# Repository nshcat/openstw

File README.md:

# openstw

A project aiming to design a physical replica of a German Sp Dr S60 relais signal box panel (_Stelltisch_) with a software simulation of local railway traffic behind it, in order to offer a compelling simulation of the day-to-day work of a signal box operator (_Fahrdienstleiter_).

## Project goals
- **A depiction of a Sp Dr S60 Stelltisch that is as realistic as possible** - This is pretty much the main goal for me. Unlike many other projects on the internet that already saw the light of day, I am not planning on making any compromises when it comes to the visual and functional design of the Stelltisch and its tiles. Even though that is likely never going to happen, I'd want it to be useable as a training aid for train routing controllers, even if only in theory.

- **Easy extensibility when adapting to new Betriebsstellen** - The system should be very modular and easy to configure, such that building replicas of any of the real German Betriebsstellen that employ a Sp Dr S60 signal box is as easy and frictionless as possible. Of course, local oddities will almost always require some degree of customization, such as custom tiles that feature specific colours and signal placements, but my goal is to reduce this work as much as possible, and make it as easy as possible.

- **As little expensive tools needed as possible** - I want the whole project to be buildable with nothing more than a run-of-the-mill 3D printer, access to a PCB manufacturing and assembly service and a set of screwdrivers. This includes not having to pay tons of money for software licenses!

- And of course, **Be completely Open-Source!** - To me, this also implies that all the tools used to make this project a reality should be open-source as well.

## Non-goals
- **Interfacing with model train setups** - I personally am neither interested in nor experienced with model train setups, and thus this project will not be designed or implemented with that in mind. Although the already existing software and hardware architecture design does leave the possibility open, if anyone else dares to try :)

- **Have everything be hand-solderable** - I have decided against this right from the start. The small size of the Stelltisch tiles make it almost a neccasity to use very small SMT components, and since access to PCB assembly is easy and comparatively cheap nowadays, I felt that it would be silly to restrict my design to being hand solderable and risk compromising my goal of realism. And one can still use a stencil, solder paste and a cheap mini hot plate to assemble the boards, if so desired.

## Repository structure

Each sub folder contains its own README file with more detailed information about that specific component of the project. Right now, the project consists of the following components:

 - `hardware`: Contains design files for the various PCBs and 3d-printed components used in the project that make up the physical Stelltisch, and act as the simulator frontend.
 - `software`: The software that simulates the signal box, including simulated time tables and train traffic. This acts as the simulator backend.
 - `firmware`: Firmware for all PCBs that contain a programmable microcontroller. The firmware handles communication with the simulator backend via CAN bus, and controlling and supervising the LEDs and input elements of each Stelltisch tile.

## Glossary
- **Stellwerk** - German term for a signalling box.
- **Fahrdienstleiter** - German term for a signal box operator.
- **Betriebsstelle** - German term for a part of the railway network that often has a Stellwerk associated with it. Often contains a public train station, but doesn't have to.
- **Sp Dr S60** - A specific kind of Stellwerk implementation based on signalling relais technology, developed by Siemens Germany in the 1960's that found wide spread adoption within the German railway infrastructure, and is still in operation today at many Betriebsstellen.
- **Stelltisch** - A big panel made up of rectangular tiles featuring a schematic depiction of the local railway topology and infrastructure of a Betriebsstelle, allowing the Fahrdienstleiter to interact with the local signalling systems to safely setup routes for trains.

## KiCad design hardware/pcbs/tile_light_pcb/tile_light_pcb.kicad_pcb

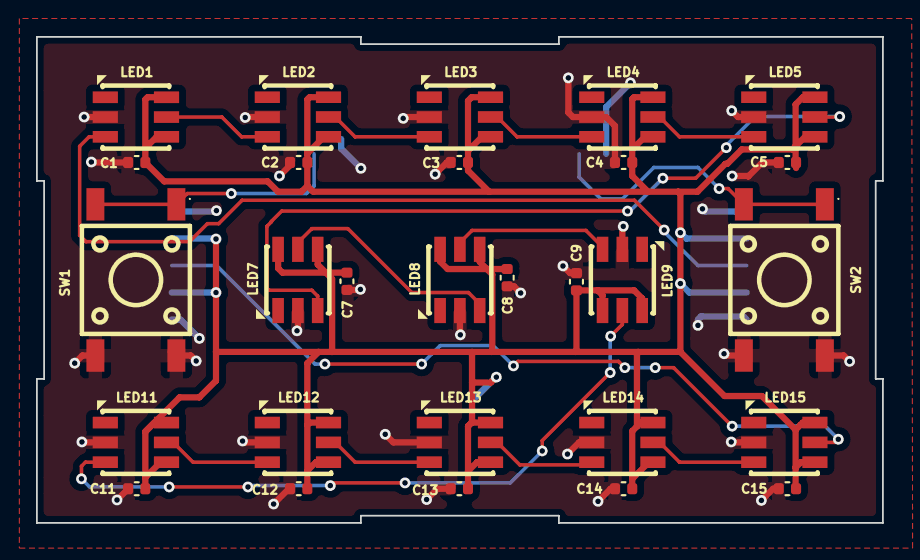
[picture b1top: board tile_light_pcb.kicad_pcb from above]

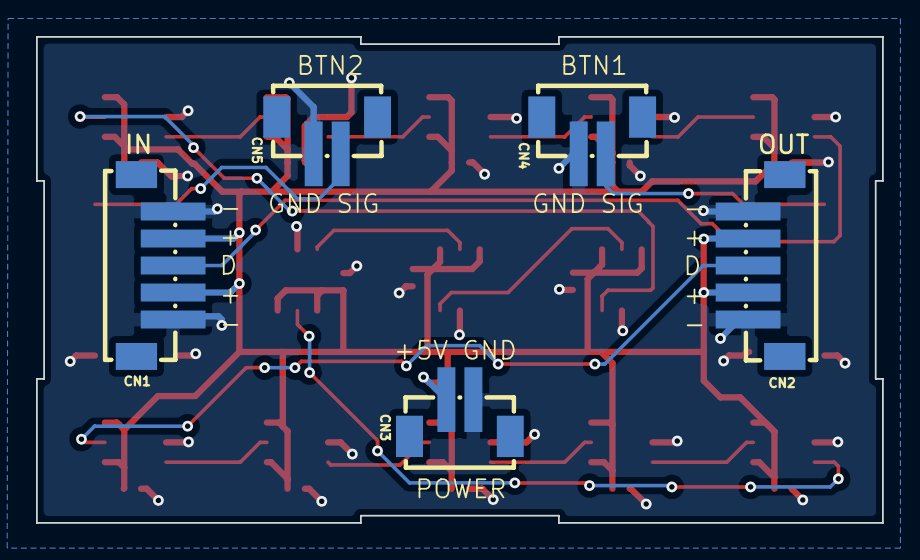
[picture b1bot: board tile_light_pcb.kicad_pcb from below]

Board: 2 copper layers, 47.0 x 27.0 mm, 33 parts (5 on the bottom side), 18 nets.

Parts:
C1, C2, C3, C4, C5, C7, C8, C9, C11, C12, C13, C14, C15: 100nF; C_0402_1005Metric
CN1, CN2: ZX-ZH1.5-5PLT; CONN-SMD_5P-P1.50_ZX-ZH1.5-5PLT
CN3, CN4, CN5: ZX-ZH1.5-2PLT; CONN-SMD_2P-P1.50_ZX-ZH1.5-2PLT
LED1, LED2, LED3, LED4, LED5, LED7, LED8, LED9, LED11, LED12, LED13, LED14, LED15: SK6812MINIRGBW-WS-P6-A; LED-SMD_6P-L3.5-W3.5_SK6812MINIRGBW-WS-P6-A
SW1, SW2: HX-6X6X7.3-TP FT SQUARE BUTTON; SW-SMD_4P-L6.0-W6.0-P4.50-LS9.0-H7.3

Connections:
+5V: C1.2, C2.2, C3.2, C4.2, C5.2, C7.2, C8.2, C9.2, C11.2, C12.2, C13.2, C14.2, C15.2, CN1.2, CN1.4, CN2.2, CN2.4, CN3.2, LED1.4 (VDD), LED1.6 (VDD), LED2.4 (VDD), LED2.6 (VDD), LED3.4 (VDD), LED3.6 (VDD), LED4.4 (VDD), LED4.6 (VDD), LED5.4 (VDD), LED5.6 (VDD), LED7.4 (VDD), LED7.6 (VDD), LED8.4 (VDD), LED8.6 (VDD), LED9.4 (VDD), LED9.6 (VDD), LED11.4 (VDD), LED11.6 (VDD), LED12.4 (VDD), LED12.6 (VDD), LED13.4 (VDD), LED13.6 (VDD), LED14.4 (VDD), LED14.6 (VDD), LED15.4 (VDD), LED15.6 (VDD)
BTN1: CN4.2, SW1.1, SW1.3
BTN2: CN5.2, SW2.1, SW2.3
GND: C1.1, C2.1, C3.1, C4.1, C5.1, C7.1, C8.1, C9.1, C11.1, C12.1, C13.1, C14.1, C15.1, CN1.1, CN1.5, CN2.1, CN2.5, CN3.1, CN4.1, CN5.1, LED1.2 (GND), LED2.2 (GND), LED3.2 (GND), LED4.2 (GND), LED5.2 (GND), LED7.2 (GND), LED8.2 (GND), LED9.2 (GND), LED11.2 (GND), LED12.2 (GND), LED13.2 (GND), LED14.2 (GND), LED15.2 (GND), SW1.2, SW1.4, SW2.2, SW2.4
LED_DIN: CN1.3, LED1.3 (DIN)
LED_DOUT: CN2.3, LED15.5 (DOUT)
unnamed: LED1.5 (DOUT), LED2.3 (DIN)
unnamed: LED2.5 (DOUT), LED3.3 (DIN)
unnamed: LED3.5 (DOUT), LED4.3 (DIN)
unnamed: LED4.5 (DOUT), LED5.3 (DIN)
unnamed: LED5.5 (DOUT), LED7.3 (DIN)
unnamed: LED7.5 (DOUT), LED8.3 (DIN)
unnamed: LED8.5 (DOUT), LED9.3 (DIN)
unnamed: LED9.5 (DOUT), LED11.3 (DIN)
unnamed: LED11.5 (DOUT), LED12.3 (DIN)
unnamed: LED12.5 (DOUT), LED13.3 (DIN)
unnamed: LED13.5 (DOUT), LED14.3 (DIN)
unnamed: LED14.5 (DOUT), LED15.3 (DIN)

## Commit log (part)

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2025-08-16 Added boost
2025-08-16 More stuff
2025-08-16 Some more work on simulation models
2025-08-17 Added pugixml dependency
2025-08-19 Lots of work on rendering code
2025-08-20 Experimenting with graphics sub items
2025-08-22 Fixed tile graphics items not receiving mouse inputs - the graphics item group containing all the tiles was swallowing the events
2025-08-24 Work on the tile rendering infrastructure
2025-08-24 More rendering code, and zoom interaction in tile view
2025-08-24 Made tile rendering more correct and without overlap
2025-08-25 Reorganized porject structure
2025-08-26 Work on signal simulation model
2025-08-27 More work on signal simulation classes
2025-08-27 Tile can now have signals in both directions
2025-08-27 Reworked how the simulation object is created, and add XML import
2025-08-27 Work on track rendering
2025-08-29 Simple track rendering
2025-08-29 WIP Rendering of Hauptsignalschirm
2025-08-31 Cleaned up and finished rendering for hauptsignalschirme
2025-08-31 Cleaned up Hp rendering code a bit more
2025-09-01 Implemented rendering of Vorsignalschirm
2025-09-03 Finished rendering of Vorsignalschirme and multi-tile signals
2025-09-03 Implemented rendering of backwards-facing signals
2025-09-03 Implemented rendering of Sperrmelder
2025-09-03 Implemented rendering of blocksignale
2025-09-03 Added simulation template to show off blocksignale
2025-09-03 Implemented arrow rendering, and added possibilty for tracks to not have occupancy lamps
2025-09-04 Implemented SVG export of tile panel
2025-09-04 Svg image export: Added title and description
2025-09-04 Moved direction arrows into their own class and adjusted XML parsing accordingly
2025-09-04 Added text rendering helpers, and implemented label rendering for Richtungspfeile
2025-09-04 Added Erlaubnisfelder to simulation, and added skeleton for renderer
2025-09-04 WIP implementation of ErlaubnisFeld rendering
2025-09-05 Correctly implemented AusfahrSperrMelder for Erlaubnisfelder
2025-09-05 Added Zugnummernanzeige to simulation
2025-09-05 First work on seven segment display rendering
2025-09-05 More seven segment digit rendering and partial zugnummernfeld rendering code
2025-09-06 ZNA label rendering in compact style
2025-09-06 Implemented track label boxes
2025-09-06 Refactored seven segment display rendering code out of ZNA graphics object
2025-09-06 Large-style ZNA rendering
2025-09-06 Implemented ZNA blinking (and global timer which was required for this)
2025-09-06 Implemented tile labels, and lots of smaller things
2025-09-06 Small changes
2025-09-06 Refactored openstw-sim to use Qt
2025-09-06 Moved simulation into background thread
2025-09-06 Fixed segfault x)
2025-09-07 Added class for Zugnummern
2025-09-08 Integrated new zugnummer class into ZNA renderer
2025-09-08 Added setters for ZNA
2025-09-08 Implemented ZST, context menu stuff etc
2025-09-10 Implemented MDI interface, and magnets
2025-09-10 Implemented magnet rotation
2025-09-10 Implemented more magnets
2025-09-10 Implemented the rest of the magnets
2025-09-11 Implemented Feststell, Dwegmelder and labels for signals
2025-09-15 Added utility function that parses tile element direction, and extended enum to support bidirectional elements
2025-09-15 Bidirectional ZST rendering
2025-09-17 Refactored Feststelltaste rendering and organization
2025-09-17 Implemented Zugdeckungssignalschirm
2025-09-17 Implemented ZugDeckungsSignal rendering
2025-09-21 Avoid adding tile component renderers twice
2025-09-21 Fixed Erlaubnisfeld not working in right direction
2025-09-24 WIP work on switches
2025-09-24 WIP work on refactoring all tile elements to derive from TileElement
2025-10-01 Implemented platform and rendering of them
2025-10-03 WIP more work on switch rendering
2025-10-03 WIP switch rendering
2026-01-05 Test commit
